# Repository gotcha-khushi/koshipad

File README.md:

# KoshiPad

KoshiPad is a compact 9-key macropad. It features a 128×32 OLED display, per-key RGB backlighting, a rotary encoder, and a custom-designed PCB and enclosure.

Made in Fusion 360

## PCB

Schematic

PCB

Made in KiCad

## Features

- 9 mechanical keys
- 128×32 OLED display
- 9× SK6812 MINI-E per-key RGB LEDs
- EC11 rotary encoder
- Seeed XIAO RP2040
- Custom PCB designed in KiCad
- Two-piece 3D printable enclosure
- Snap-fit lip-and-groove case design
- KMK Firmware

## CAD Model

The enclosure consists of two printed parts:

- Top case
- Bottom case

The PCB is mounted inside the bottom case using M3 hardware, while the top and bottom enclosure are secured using a snap-fit lip-and-groove mechanism for a clean, screw-free exterior.

## Firmware

working on it

## Bill of Materials

Everything required to assemble the macropad:

- 1× Seeed XIAO RP2040
- 9× Cherry MX-compatible switches
- 9× DSA keycaps
- 9× SK6812 MINI-E RGB LEDs
- 9× 1N4148 DO-35 diodes
- 1× EC11 rotary encoder
- 1× 0.91" 128×32 OLED display
- 4× M3×5×4 mm heat-set inserts
- 4× M3×16 mm screws
- 1× Custom PCB
- 1× Two-piece 3D printed enclosure

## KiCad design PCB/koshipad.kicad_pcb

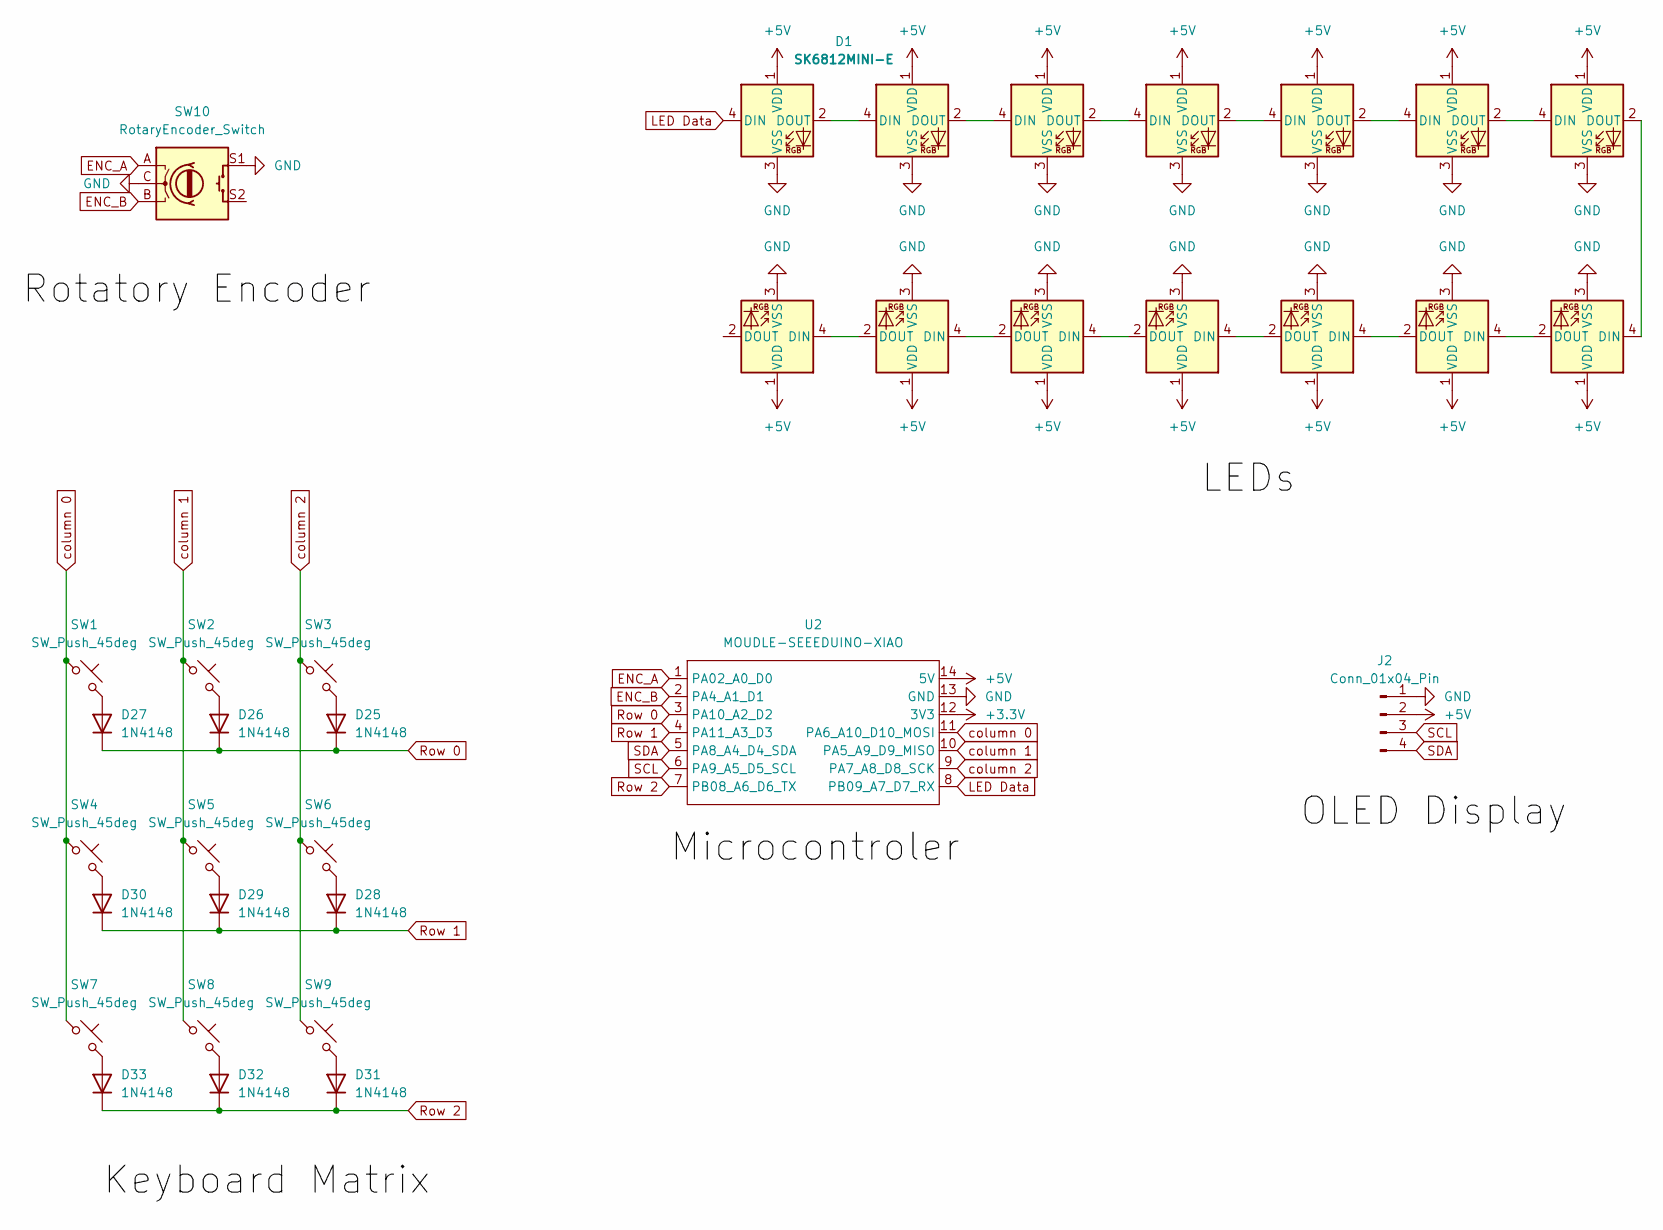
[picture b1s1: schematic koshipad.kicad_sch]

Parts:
D1, D2, D3, D4, D5, D6, D7, D8, D9, D10, D11, D12, D13, D14: SK6812MINI-E; SK6812MINI-E_fixed
D25, D26, D27, D28, D29, D30, D31, D32, D33: 1N4148; D_DO-35_SOD27_P7.62mm_Horizontal
J2: Conn_01x04_Pin; PinHeader_1x04_P2.54mm_Vertical
SW1, SW2, SW3, SW4, SW5, SW6, SW7, SW8, SW9: SW_Push_45deg; SW_Cherry_MX_1.00u_PCB
SW10: RotaryEncoder_Switch; RotaryEncoder_Alps_EC11E-Switch_Vertical_H20mm
U2: MOUDLE-SEEEDUINO-XIAO; XIAO-Generic-Hybrid-14P-2.54-21X17.8MM

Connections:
+3.3V: U2.12 (3V3)
+5V: D1.1 (VDD), D2.1 (VDD), D3.1 (VDD), D4.1 (VDD), D5.1 (VDD), D6.1 (VDD), D7.1 (VDD), D8.1 (VDD), D9.1 (VDD), D10.1 (VDD), D11.1 (VDD), D12.1 (VDD), D13.1 (VDD), D14.1 (VDD), J2.2, U2.14 (5V)
ENC_A: SW10.A, U2.1 (PA02_A0_D0)
ENC_B: SW10.B, U2.2 (PA4_A1_D1)
GND: D1.3 (VSS), D2.3 (VSS), D3.3 (VSS), D4.3 (VSS), D5.3 (VSS), D6.3 (VSS), D7.3 (VSS), D8.3 (VSS), D9.3 (VSS), D10.3 (VSS), D11.3 (VSS), D12.3 (VSS), D13.3 (VSS), D14.3 (VSS), J2.1, SW10.C, SW10.S1, U2.13 (GND)
LED Data: D1.4 (DIN), U2.8 (PB09_A7_D7_RX)
unnamed: D1.2 (DOUT), D3.4 (DIN)
unnamed: D2.4 (DIN), D4.2 (DOUT)
unnamed: D3.2 (DOUT), D5.4 (DIN)
unnamed: D4.4 (DIN), D6.2 (DOUT)
unnamed: D5.2 (DOUT), D7.4 (DIN)
unnamed: D6.4 (DIN), D8.2 (DOUT)
unnamed: D7.2 (DOUT), D9.4 (DIN)
unnamed: D10.4 (DIN), D12.2 (DOUT)
unnamed: D8.4 (DIN), D10.2 (DOUT)
unnamed: D9.2 (DOUT), D11.4 (DIN)
unnamed: D11.2 (DOUT), D13.4 (DIN)
unnamed: D12.4 (DIN), D14.2 (DOUT)
unnamed: D13.2 (DOUT), D14.4 (DIN)
unnamed: D25.2 (A), SW3.2
unnamed: D26.2 (A), SW2.2
unnamed: D27.2 (A), SW1.2
unnamed: D28.2 (A), SW6.2
unnamed: D29.2 (A), SW5.2
unnamed: D30.2 (A), SW4.2
unnamed: D31.2 (A), SW9.2
unnamed: D32.2 (A), SW8.2
unnamed: D33.2 (A), SW7.2
Row 0: D25.1 (K), D26.1 (K), D27.1 (K), U2.3 (PA10_A2_D2)
Row 1: D28.1 (K), D29.1 (K), D30.1 (K), U2.4 (PA11_A3_D3)
Row 2: D31.1 (K), D32.1 (K), D33.1 (K), U2.7 (PB08_A6_D6_TX)
SCL: J2.3, U2.6 (PA9_A5_D5_SCL)
SDA: J2.4, U2.5 (PA8_A4_D4_SDA)
column 0: SW1.1, SW4.1, SW7.1, U2.11 (PA6_A10_D10_MOSI)
column 1: SW2.1, SW5.1, SW8.1, U2.10 (PA5_A9_D9_MISO)
column 2: SW3.1, SW6.1, SW9.1, U2.9 (PA7_A8_D8_SCK)

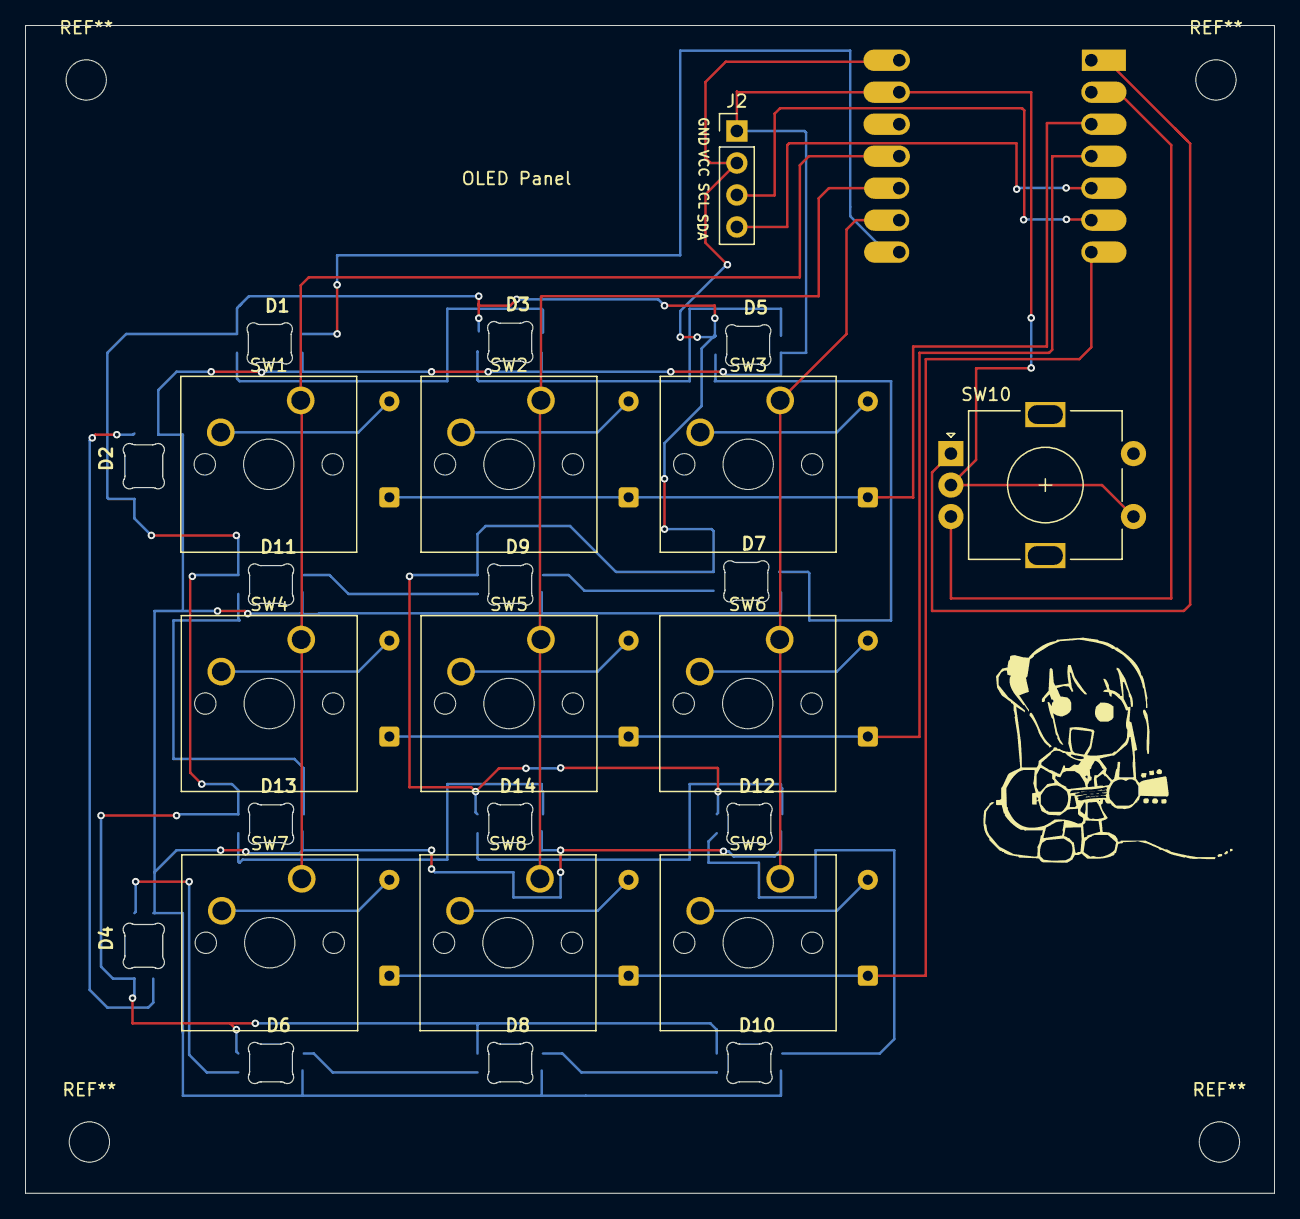
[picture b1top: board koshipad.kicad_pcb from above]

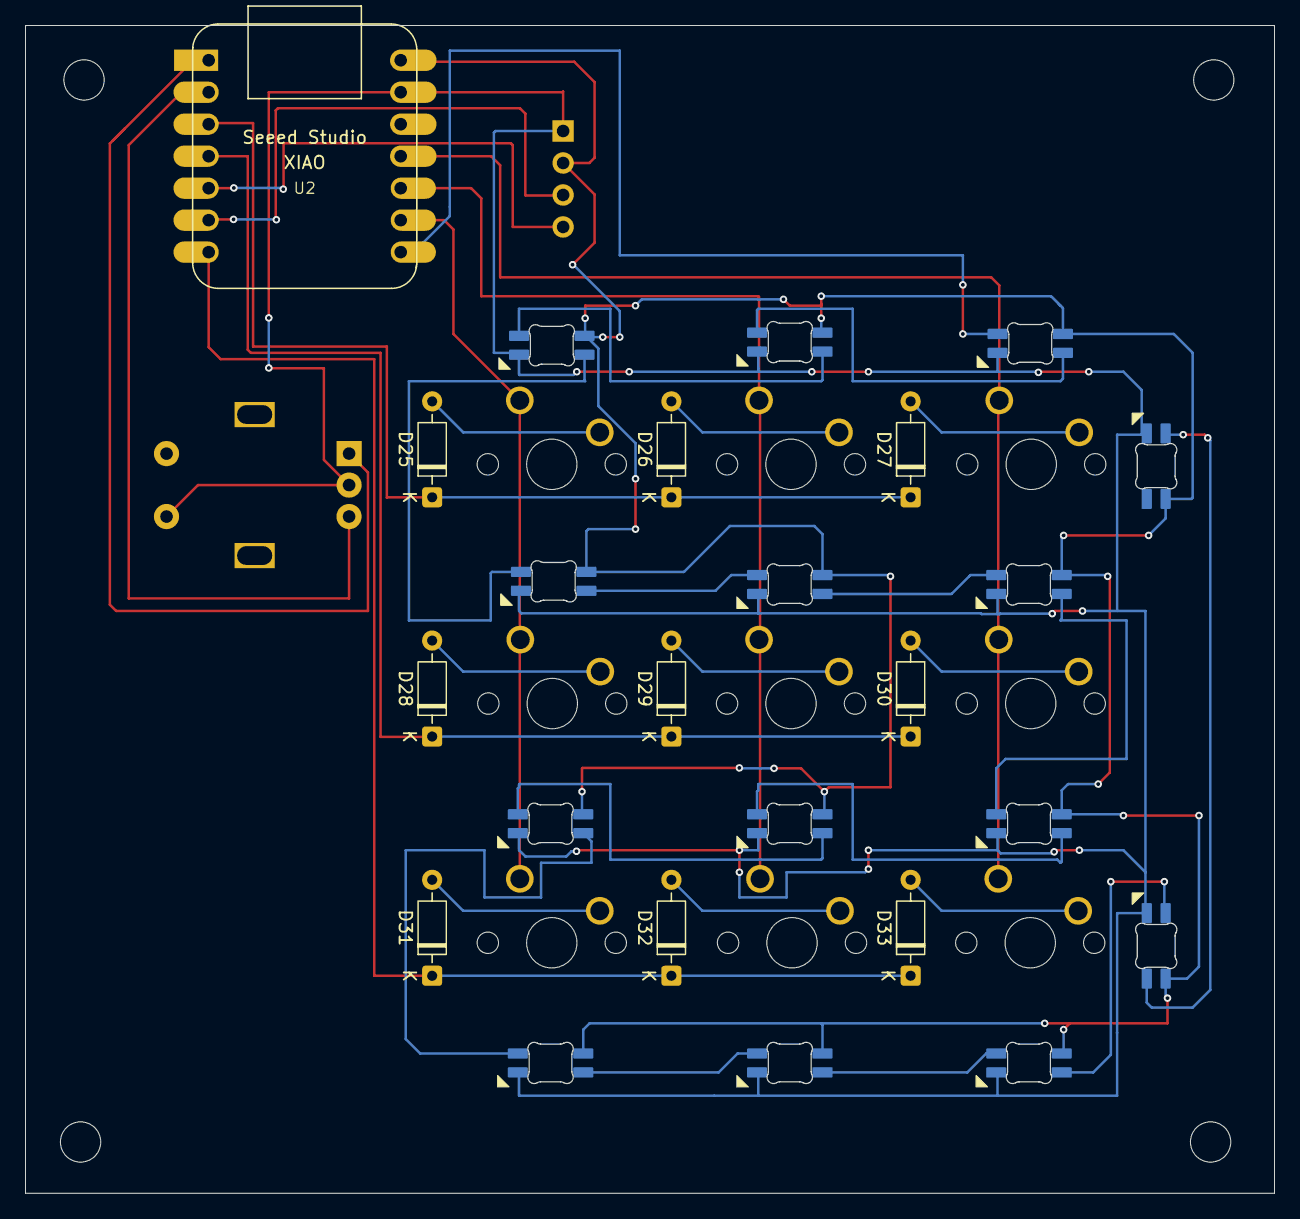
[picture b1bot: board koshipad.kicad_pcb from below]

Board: 2 copper layers, 99.1 x 92.7 mm, 35 parts (10 on the bottom side), 35 nets.

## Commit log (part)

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2026-06-05 added kicad files
2026-06-05 added pcb folder
2026-06-05 added libaries
2026-06-05 adeed schema and libraries
2026-06-05 microcotroler schema
2026-06-05 modified gitignore
2026-06-05 switch and diode schema
2026-06-11 schematic done yaaaay
2026-06-12 assigned footprints
2026-06-12 diode placement
2026-06-16 placed LEDs
2026-06-17 pcb finally done with 64 fucking errorss
2026-06-19 added bocchi sticker in PCB
2026-06-20 added greber files
2026-06-20 upadated grebers
2026-06-20 made changes in pcb
2026-06-26 3D model of componets added
